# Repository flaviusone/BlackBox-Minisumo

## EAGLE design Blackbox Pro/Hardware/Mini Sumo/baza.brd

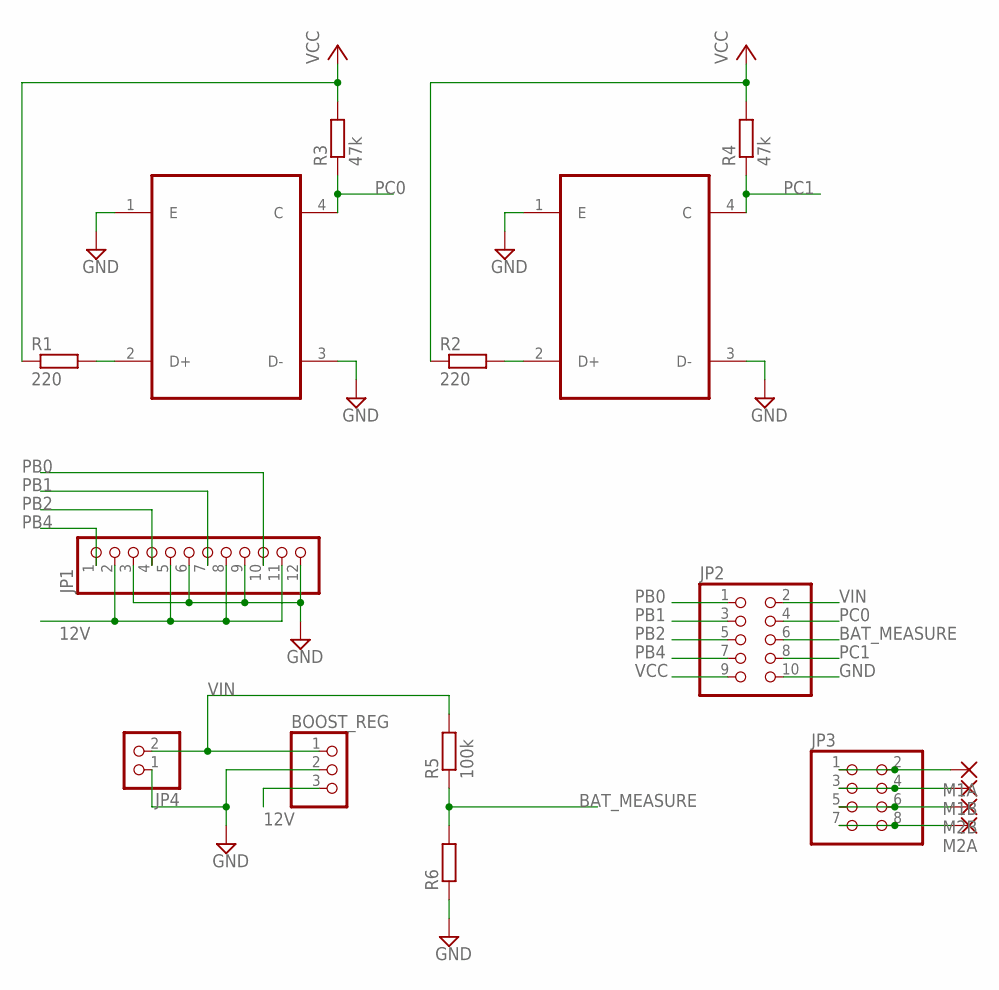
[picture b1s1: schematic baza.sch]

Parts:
BOOST_REG: PINHD-1X3; 1X03
IR1, IR2: TCNT2000
JP1: PINHD-1X12-CB; 1X12-CB
JP2: PINHD-2X5; 2X05
JP3: PINHD-2X4; 2X04
JP4: PINHD-1X2; 1X02
M1A, M1B, M2A, M2B: 2,15/1,0
R1, R2: 220; M1206
R3, R4: 47k; M1206
R5: 100k; R1206
R6: R-EU_R1206; R1206

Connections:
12V: BOOST_REG.3, JP1.2, JP1.5, JP1.8, JP1.11
BAT_MEASURE: JP2.6, R5.1, R6.2
GND: BOOST_REG.2, IR1.1 (E), IR1.3 (D-), IR2.1 (E), IR2.3 (D-), JP1.3, JP1.6, JP1.9, JP1.12, JP2.10, JP4.1, R6.1
unnamed: IR1.2 (D+), R1.2
unnamed: JP3.1, JP3.2, M1A.1
unnamed: IR2.2 (D+), R2.2
unnamed: JP3.3, JP3.4, M1B.1
unnamed: JP3.5, JP3.6, M2B.1
unnamed: JP3.7, JP3.8, M2A.1
PB0: JP1.10, JP2.1
PB1: JP1.7, JP2.3
PB2: JP1.4, JP2.5
PB4: JP1.1, JP2.7
PC0: IR1.4 (C), JP2.4, R3.1
PC1: IR2.4 (C), JP2.8, R4.1
VCC: JP2.9, R1.1, R2.1, R3.2, R4.2
VIN: BOOST_REG.1, JP2.2, JP4.2, R5.2

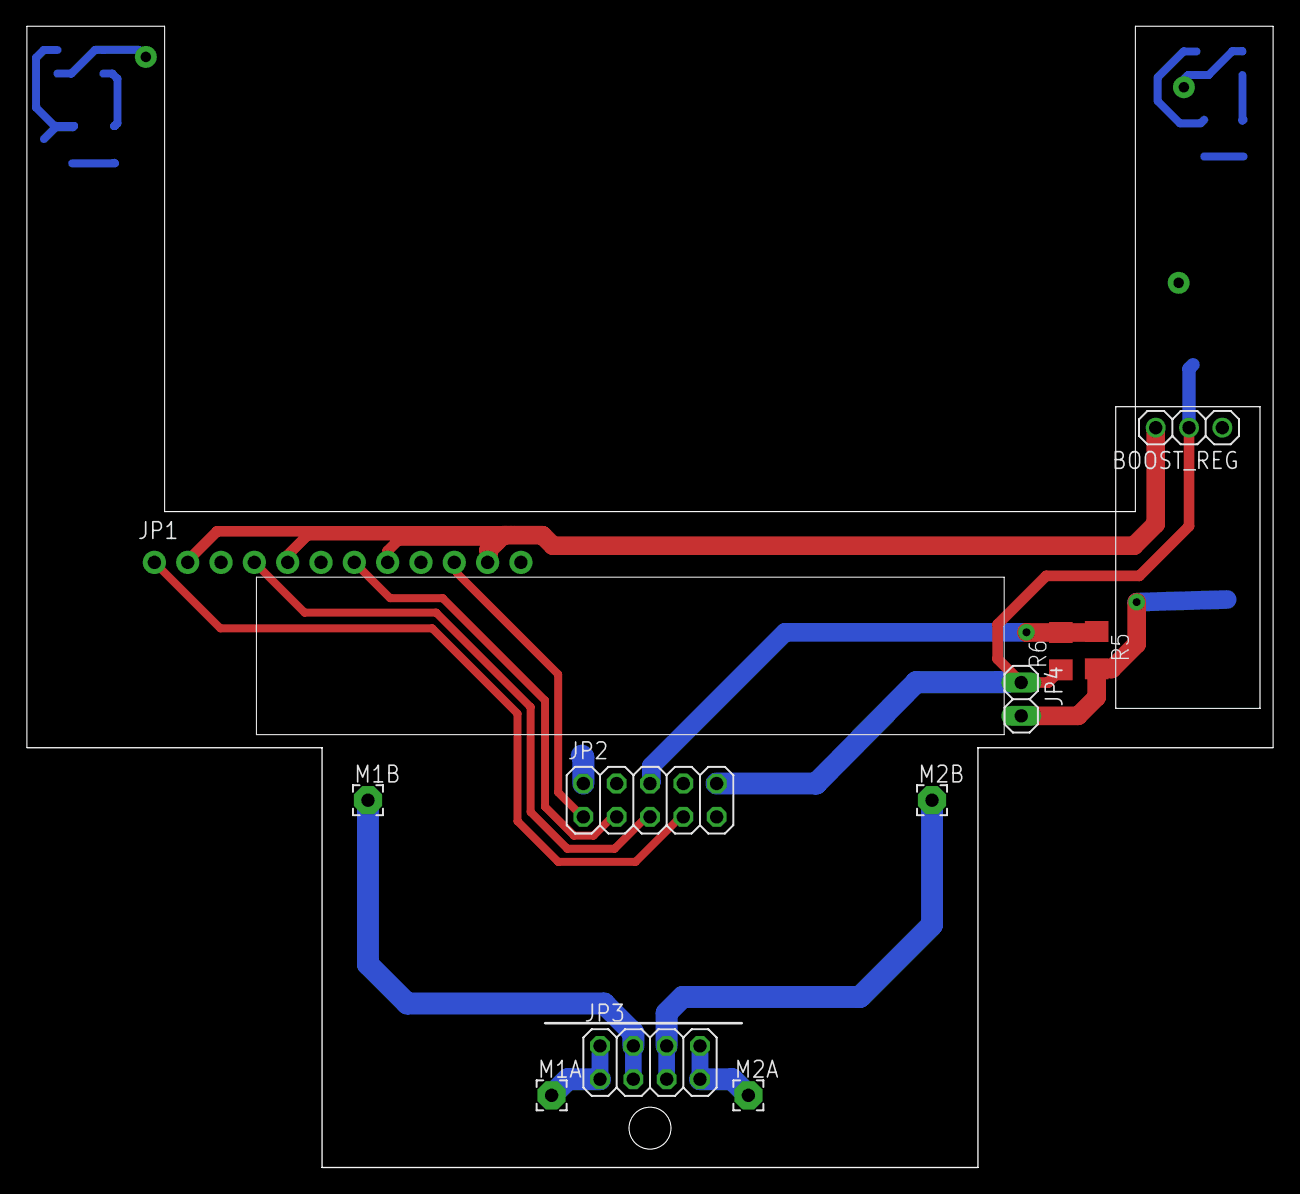
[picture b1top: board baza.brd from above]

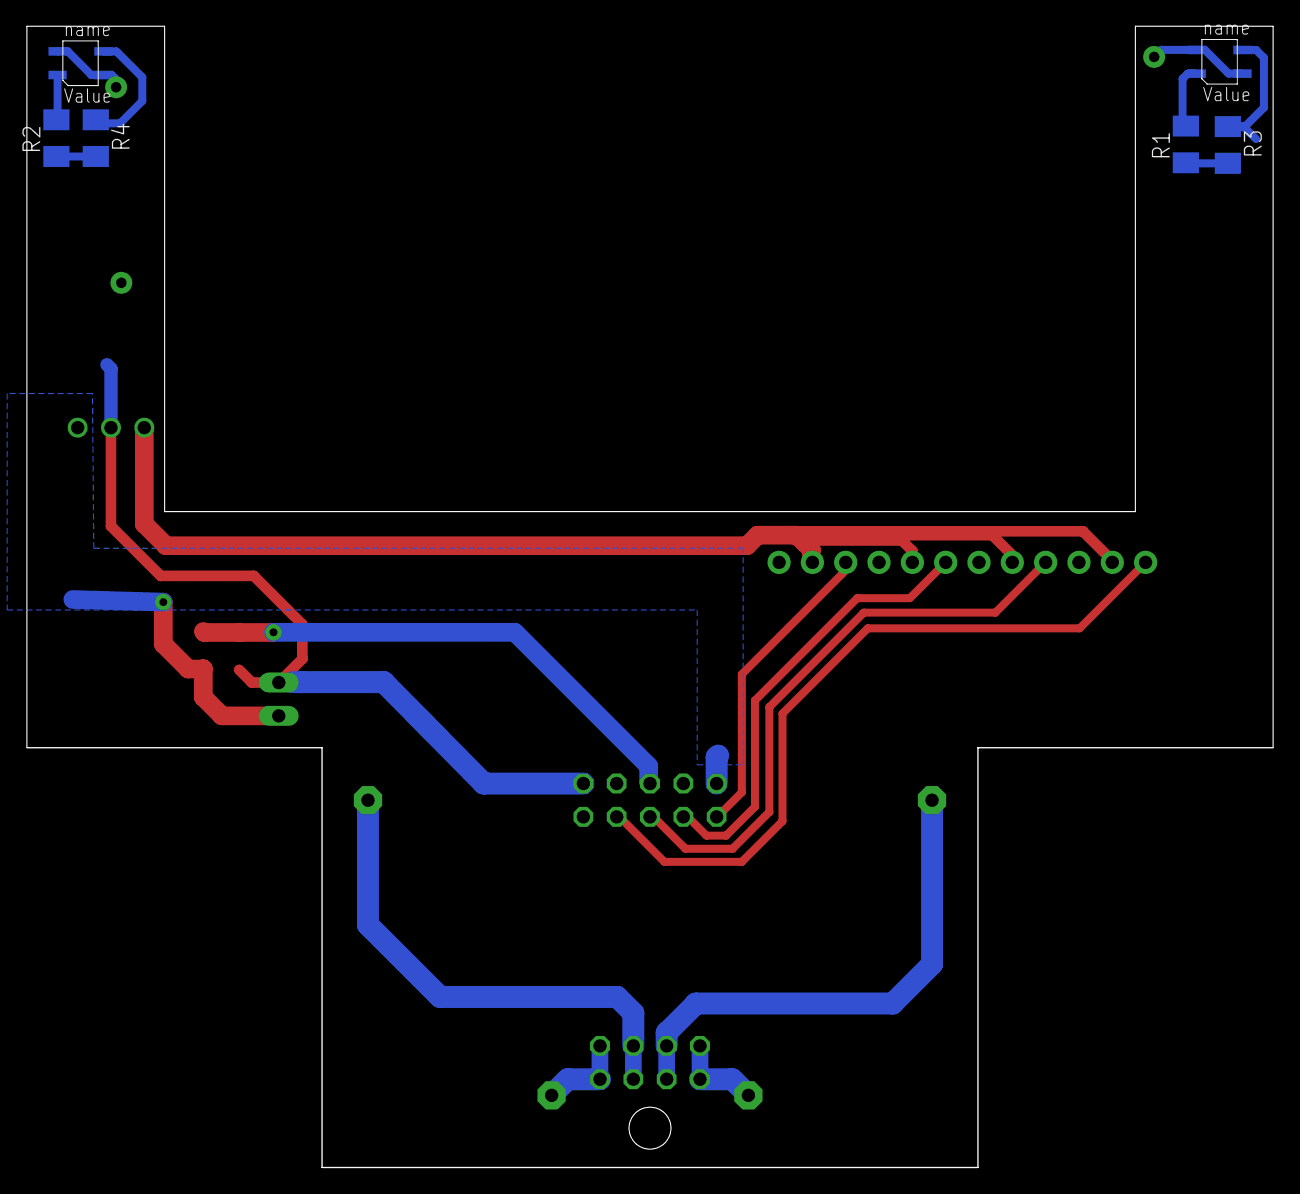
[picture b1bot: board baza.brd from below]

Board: 2 copper layers, 95.0 x 87.0 mm, 17 parts (6 on the bottom side), 17 nets.

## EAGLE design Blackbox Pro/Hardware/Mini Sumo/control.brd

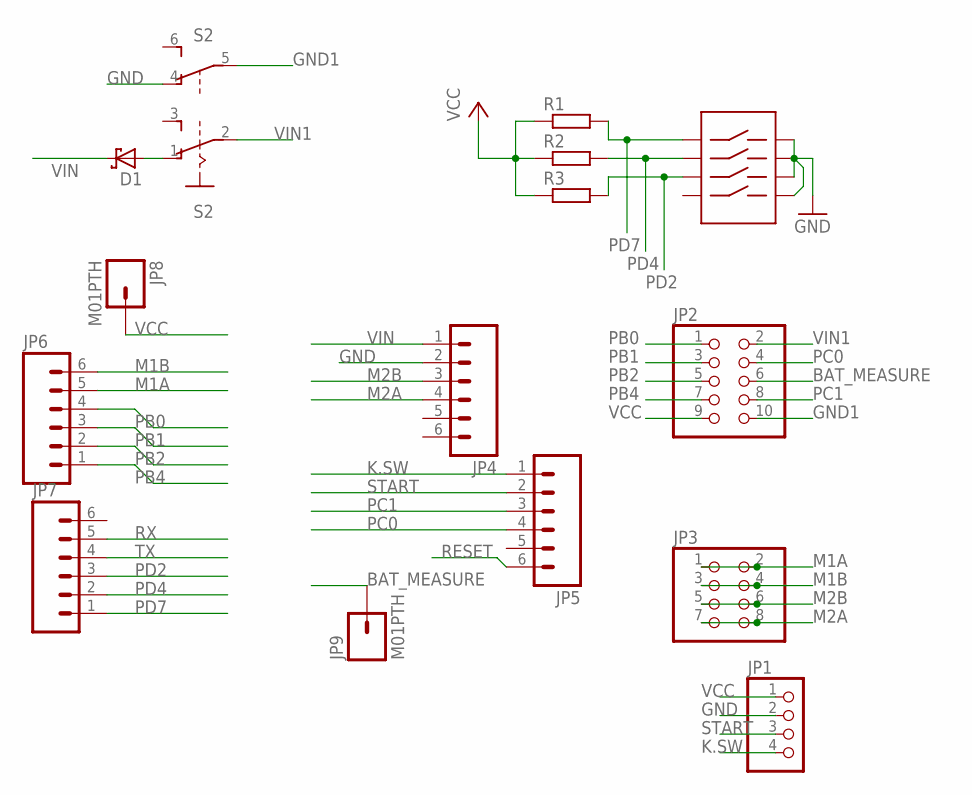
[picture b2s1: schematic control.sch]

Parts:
D1: SCHOTTKY-DIODESMC; SMC
JP1: PINHD-1X4; 1X04
JP2: PINHD-2X5; 2X05
JP3: PINHD-2X4; 2X04
JP4, JP5, JP6, JP7: M06SMD-STRAIGHT; 1X06_SMD_STRAIGHT
JP8, JP9: M01PTH; 1X01
R1, R2, R3: R-EU_R0805; R0805
S2: A68-A31
U$2: DGH04; GDH04

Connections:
BAT_MEASURE: JP2.6, JP9.1
GND: JP1.2, JP4.2, S2.4 (O), U$2.P$1, U$2.P$6, U$2.P$7, U$2.P$8
GND1: JP2.10, S2.5
K.SW: JP1.4, JP5.1
M1A: JP3.1, JP3.2, JP6.5
M1B: JP3.3, JP3.4, JP6.6
M2A: JP3.7, JP3.8, JP4.4
M2B: JP3.5, JP3.6, JP4.3
unnamed: D1.A, S2.1 (O)
PB0: JP2.1, JP6.4
PB1: JP2.3, JP6.3
PB2: JP2.5, JP6.2
PB4: JP2.7, JP6.1
PC0: JP2.4, JP5.4
PC1: JP2.8, JP5.3
PD2: JP7.3, R3.2, U$2.P$4
PD4: JP7.2, R2.2, U$2.P$3
PD7: JP7.1, R1.2, U$2.P$2
RESET: JP5.6
RX: JP7.5
START: JP1.3, JP5.2
TX: JP7.4
VCC: JP1.1, JP2.9, JP8.1, R1.1, R2.1, R3.1
VIN: D1.C, JP4.1
VIN1: JP2.2, S2.2

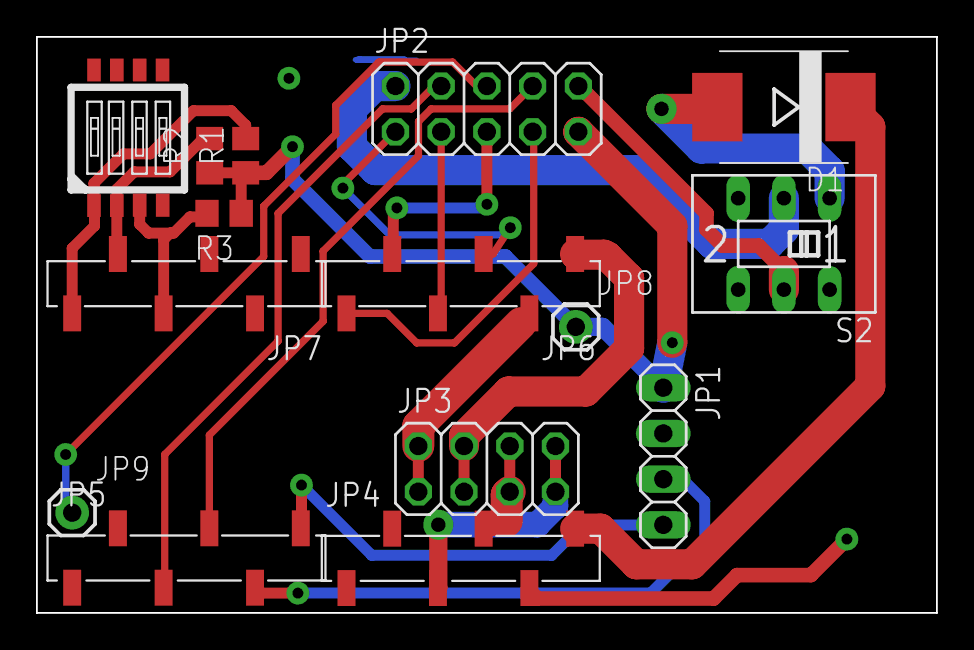
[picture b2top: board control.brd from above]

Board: 2 copper layers, 50.0 x 32.0 mm, 15 parts (0 on the bottom side), 22 nets.

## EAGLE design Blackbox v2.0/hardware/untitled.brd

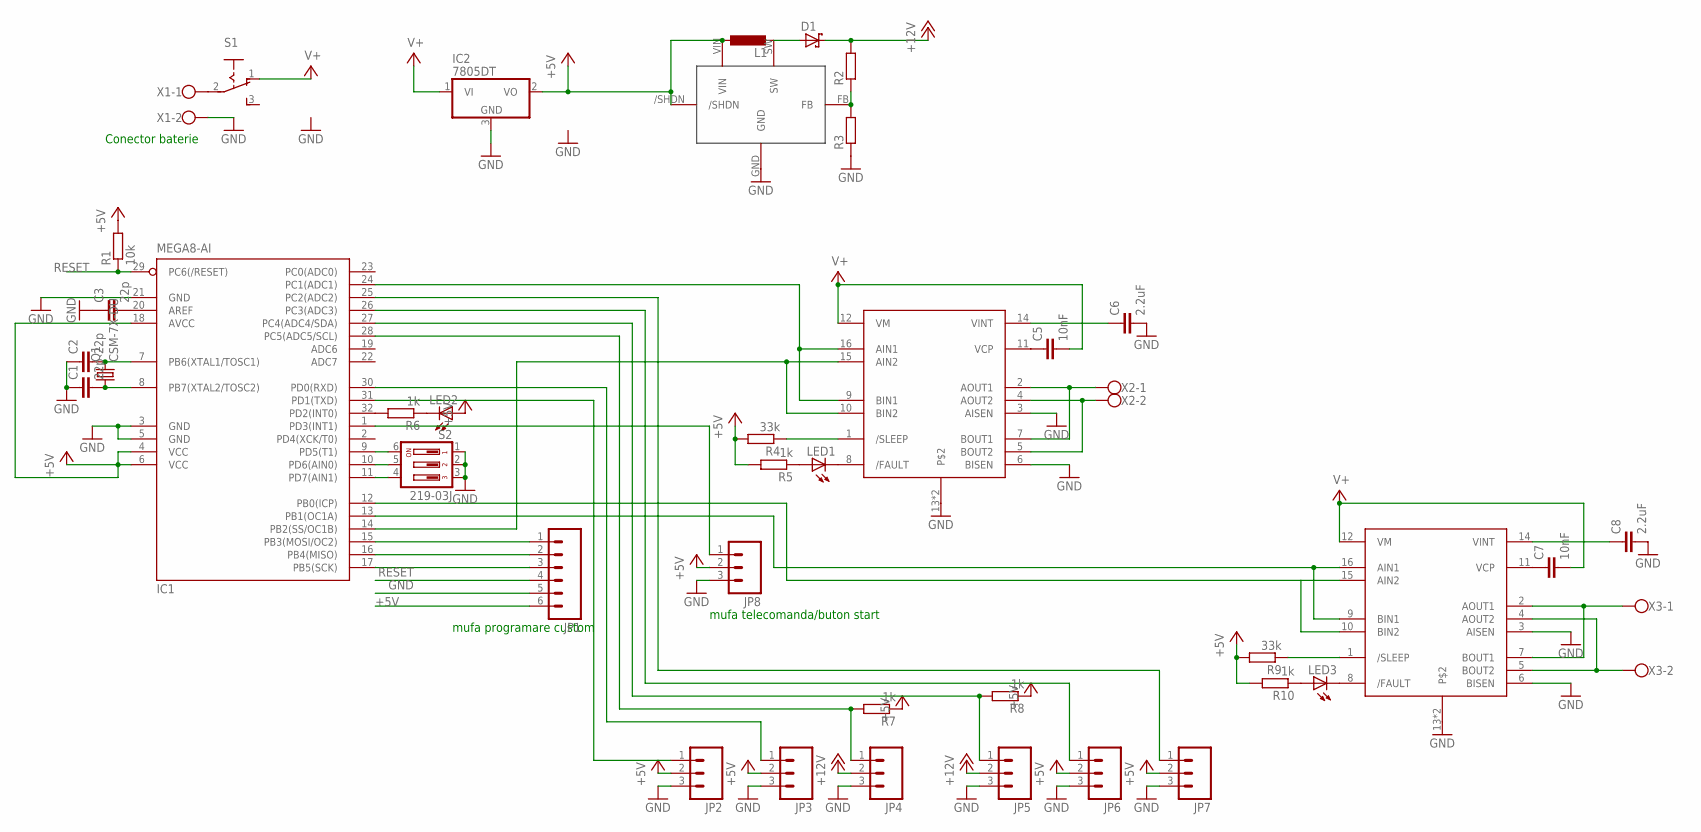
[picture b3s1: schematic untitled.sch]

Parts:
C1, C2, C3: 22p; C0805
C5, C7: 10nF; C0805
C6, C8: 2.2uF; C0805
D1: SCHOTTKY-DIODESMD; SMB
IC1: MEGA8-AI; TQFP32-08
IC2: 7805DT; TO252
JP1: M06SIP; 1X06
JP2, JP3, JP4, JP5, JP6, JP7, JP8: M03PTH; 1X03
L1: L-EUL4532C; L4532M
LED1, LED2, LED3: LEDSML0805; SML0805
Q1: CSM-7X-DU
R1: 10k; R0805
R2, R3: R-EU_R0805; R0805
R4, R9: 33k; R0805
R5, R6, R7, R8, R10: 1k; R0805
S1: 255SB
S2: 219-03J; CTS-219-03J
U$1: LM2703; SOT23
U$2, U$3: DRV8833-PWP; PW
X1, X2, X3: W237-102

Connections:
+5V: IC1.4 (VCC), IC1.6 (VCC), IC1.18 (AVCC), IC2.2 (VO), JP1.6, JP2.2, JP3.2, JP6.2, JP7.2, JP8.2, L1.1, LED2.A, R1.2, R4.2, R5.2, R7.1, R8.1, R9.2, R10.2, U$1./SHDN, U$1.VIN
+12V: D1.C, JP4.2, JP5.2, R2.2
GND: C1.1, C2.1, C3.1, C6.2, C8.2, IC1.3 (GND), IC1.5 (GND), IC1.21 (GND), IC2.3 (GND), JP1.5, JP2.3, JP3.3, JP4.3, JP5.3, JP6.3, JP7.3, JP8.3, R3.1, S2.1, S2.2, S2.3, U$1.GND, U$2.3 (AISEN), U$2.6 (BISEN), U$2.13, U$2.PAD, U$3.3 (AISEN), U$3.6 (BISEN), U$3.13, U$3.PAD, X1.2
unnamed: C2.2, IC1.7 (PB6(XTAL1/TOSC1)), Q1.2
unnamed: C1.2, IC1.8 (PB7(XTAL2/TOSC2)), Q1.1
unnamed: S1.2, X1.1
unnamed: IC1.17 (PB5(SCK)), JP1.3
unnamed: IC1.16 (PB4(MISO)), JP1.2
unnamed: IC1.15 (PB3(MOSI/OC2)), JP1.1
unnamed: D1.A, L1.2, U$1.SW
unnamed: R4.1, U$2.1 (/SLEEP)
unnamed: R2.1, R3.2, U$1.FB
unnamed: LED1.C, U$2.8 (/FAULT)
unnamed: LED1.A, R5.1
unnamed: U$2.2 (AOUT1), U$2.7 (BOUT1), X2.1
unnamed: U$2.4 (AOUT2), U$2.5 (BOUT2), X2.2
unnamed: R9.1, U$3.1 (/SLEEP)
unnamed: LED3.C, U$3.8 (/FAULT)
unnamed: C5.1, U$2.11 (VCP)
unnamed: C6.1, U$2.14 (VINT)
unnamed: IC1.12 (PB0(ICP)), U$3.10 (BIN2), U$3.15 (AIN2)
unnamed: IC1.24 (PC1(ADC1)), U$2.9 (BIN1), U$2.16 (AIN1)
unnamed: IC1.13 (PB1(OC1A)), U$3.9 (BIN1), U$3.16 (AIN1)
unnamed: IC1.14 (PB2(SS/OC1B)), U$2.10 (BIN2), U$2.15 (AIN2)
unnamed: IC1.9 (PD5(T1)), S2.6
unnamed: IC1.10 (PD6(AIN0)), S2.5
unnamed: IC1.11 (PD7(AIN1)), S2.4
unnamed: IC1.1 (PD3(INT1)), JP8.1
unnamed: IC1.31 (PD1(TXD)), JP2.1
unnamed: IC1.30 (PD0(RXD)), JP3.1
unnamed: IC1.28 (PC5(ADC5/SCL)), JP4.1, R7.2
unnamed: IC1.27 (PC4(ADC4/SDA)), JP5.1, R8.2
unnamed: IC1.26 (PC3(ADC3)), JP6.1
unnamed: IC1.25 (PC2(ADC2)), JP7.1
unnamed: IC1.32 (PD2(INT0)), R6.2
unnamed: LED2.C, R6.1
unnamed: LED3.A, R10.1
unnamed: C7.1, U$3.11 (VCP)
unnamed: C8.1, U$3.14 (VINT)
unnamed: C3.2, IC1.20 (AREF)
unnamed: U$3.4 (AOUT2), U$3.5 (BOUT2), X3.2
unnamed: U$3.2 (AOUT1), U$3.7 (BOUT1), X3.1
RESET: IC1.29 (PC6(/RESET)), JP1.4, R1.1
V+: C5.2, C7.2, IC2.1 (VI), S1.1 (O), U$2.12 (VM), U$3.12 (VM)

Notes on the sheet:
Conector baterie
mufa telecomanda/buton start
mufa programare custom

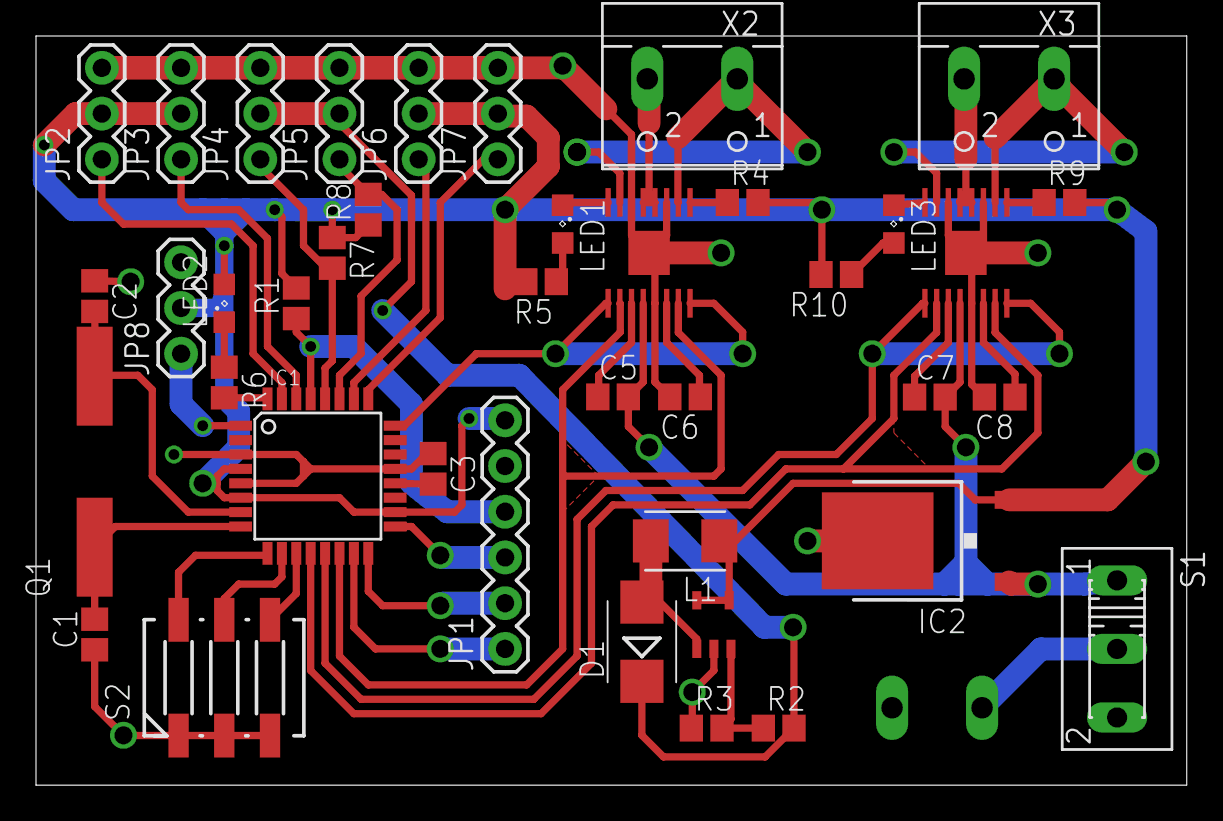
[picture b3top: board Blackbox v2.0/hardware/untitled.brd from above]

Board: 2 copper layers, 63.9 x 41.6 mm, 41 parts (1 on the bottom side), 44 nets.

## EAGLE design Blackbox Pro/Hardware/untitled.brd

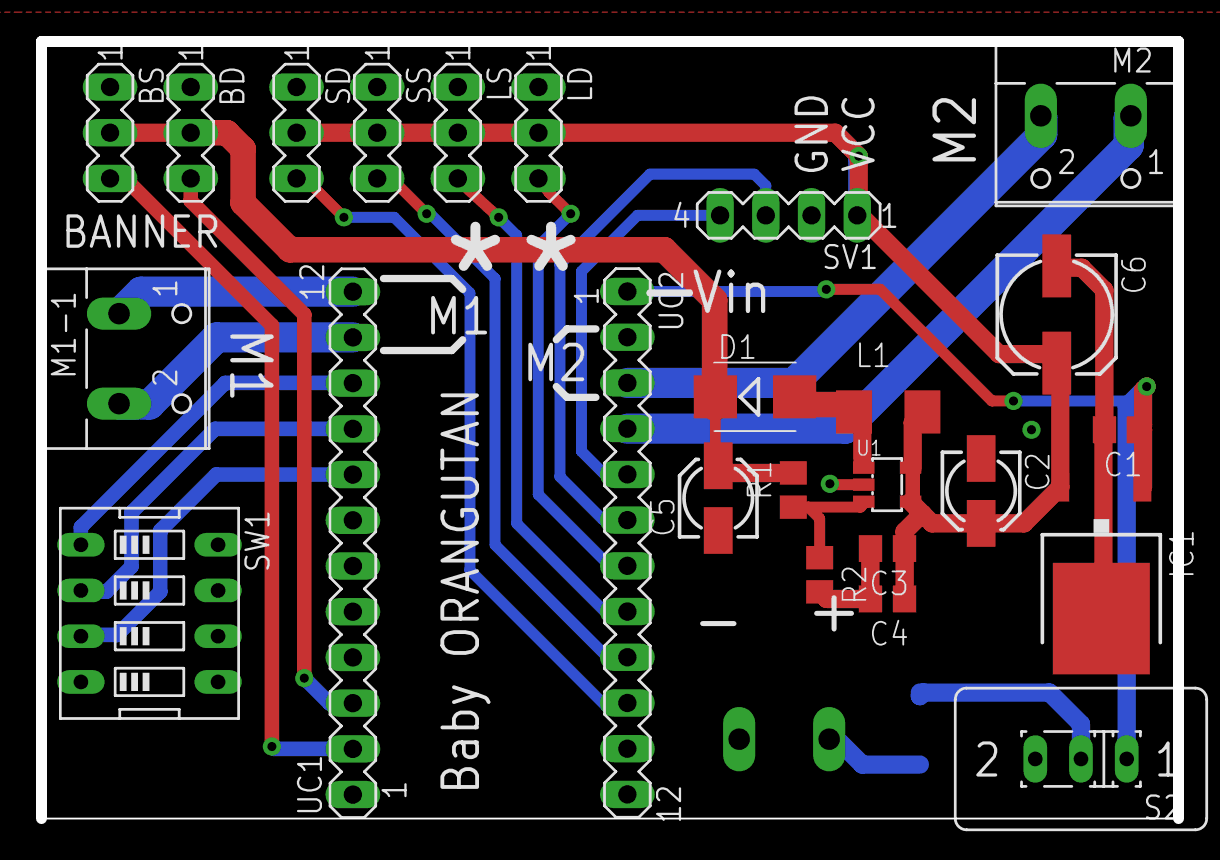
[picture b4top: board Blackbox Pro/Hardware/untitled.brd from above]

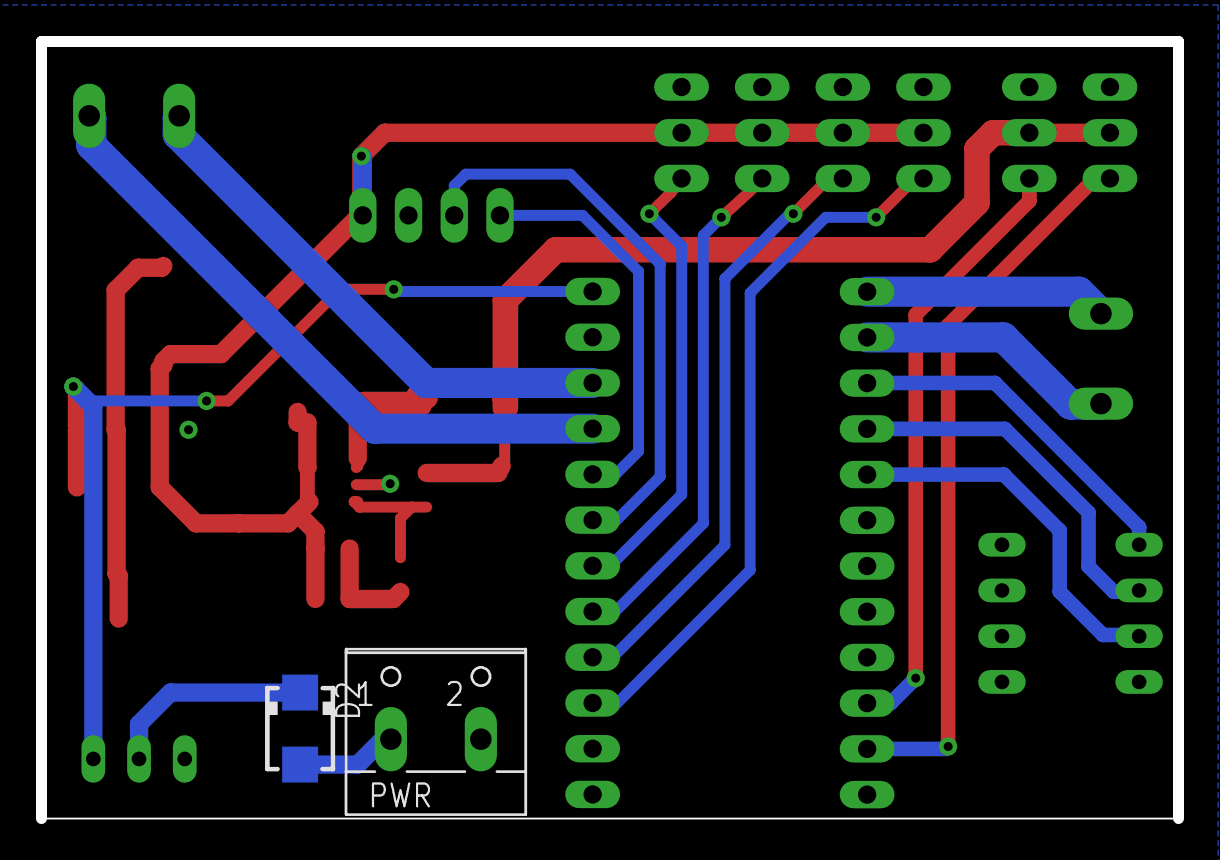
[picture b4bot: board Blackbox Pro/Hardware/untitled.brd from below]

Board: 2 copper layers, 63.2 x 43.2 mm, 27 parts (2 on the bottom side), 23 nets.

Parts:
BD: MA03-1
BS: MA03-1
C1: 0.33uF; C0805
C2, C5: 4.7uF; 153CLV-0405
C3: 100n; C0805
C4: 0.1uF; C0805
C6: 153CLV-0605
D1: SMB
D2: PMEG3050EP; SMA
IC1: 7805DT; TO252
L1: L4532M
LD: MA03-1
LS: MA03-1
M1-1, M2: W237-102
PWR: W237-102
R1, R2: R0805
S2: M251
SD: MA03-1
SS: MA03-1
SV1: MA04-1
SW1: EDG-04
U1: LM2703-SOT23-5; SOT23-5
UC1, UC2: MA12-1

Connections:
+5V: C2.+, C3.1, C4.1, C6.+, IC1.2, L1.2, LD.2, LS.2, SD.2, SS.2, SV1.1, U1.4, U1.5
+12V: BD.2, BS.2, C5.+, D1.C, R1.2
GND: BD.1, BS.1, C1.2, C2.-, C3.2, C4.2, C5.-, C6.-, IC1.3, LD.1, LS.1, PWR.2, R2.2, SD.1, SS.1, SV1.2, SW1.6, SW1.7, SW1.8, U1.2, UC2.2
M1.1: M1-1.2, UC1.11
M1.2: M1-1.1, UC1.12
M2.1: M2.2, UC2.3
M2.2: M2.1, UC2.4
unnamed: D1.A, L1.1, U1.1
unnamed: D2.A, PWR.1
unnamed: D2.C, S2.2
unnamed: R1.1, R2.1, U1.3
PB0: SW1.1, UC1.10
PB1: SW1.2, UC1.9
PB2: SW1.3, UC1.8
PC0: SD.3, UC2.10
PC1: SS.3, UC2.9
PC2: LS.3, UC2.8
PC3: LD.3, UC2.7
PC4: SV1.3, UC2.6
PC5: SV1.4, UC2.5
PD2: BD.3, UC1.3
PD4: BS.3, UC1.2
V+: C1.1, IC1.1, S2.1, UC2.1

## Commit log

2013-04-10 Mass Add
2013-04-23 Added millis to avid line
2013-04-23 Removed millis from line avoid
2013-04-23 Added strategy function
2013-04-23 Corrected strategy pins
2013-04-23 Added strategy implementation
2013-04-23 Scos bullshit
2013-04-23 Adaugat viteze rapide la evitari
2013-04-23 Adaugat conditii pentru evitare bannere
2013-04-23 Cod pt debug viteze
2013-04-23 Incercare rotire bannere cu delay
2013-04-23 Incearcare fara delay cu millis
2013-04-23 mers triunghi
2013-04-23 Modificari evitare linie
2013-04-23 atac + atac2
2013-04-23 Varianta cu rotire doar cu o roata la iesirea din teren
2013-04-24 Varianta 1.0
2013-04-24 Varianta 2.0
2013-10-20 Mutat fisiere in Blackbox v1.0
2013-10-20 Adaugat fisiere HW si SW pt ver noua
2013-10-31 Testat new branch
2013-11-01 Add Motors::drive function
2013-11-02 Adaug placa in versiunea noua
    (mufa de programare cu 6 pini si condensator pt ADC)
2013-11-21 Blackbox v2.1 is alive !
2013-11-21 Adaugat pinout mapping
2013-11-21 Monitor Senzori - Citiri bannere
2013-11-21 Add Test_motoare
2013-11-21 Add monitorizare senzori
2013-11-22 Add citiri Strategy + Line
2013-11-22 Fisiere test
2013-11-22 Added sketch for program
2013-11-22 Initial Files+Working Start-Sop & Select Strategy
2013-11-22 Adaugat fisiere ce lipseau
2013-11-22 Adaugat strategie de test
2013-11-23 Shit Add
2013-11-24 Modificare senzor telecomanda (inca e ciudat)
2014-04-27 Reparat glitch lateral
2014-05-01 Blackbox Pro
2014-05-03 Added schematics + code changes
2014-05-08 Updatat cod cu delay pt senzori laterala.
2014-05-09 Locul 3 la locala
2014-11-06 Bug fixes
    Disablat senzorii laterali pe Pro. Reparat bug directie default.

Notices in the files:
parts and their libraries:
SparkFun-Connectors: Licensing: CC v3.0 Share-Alike You are welcome to use this library for commercial purposes.
